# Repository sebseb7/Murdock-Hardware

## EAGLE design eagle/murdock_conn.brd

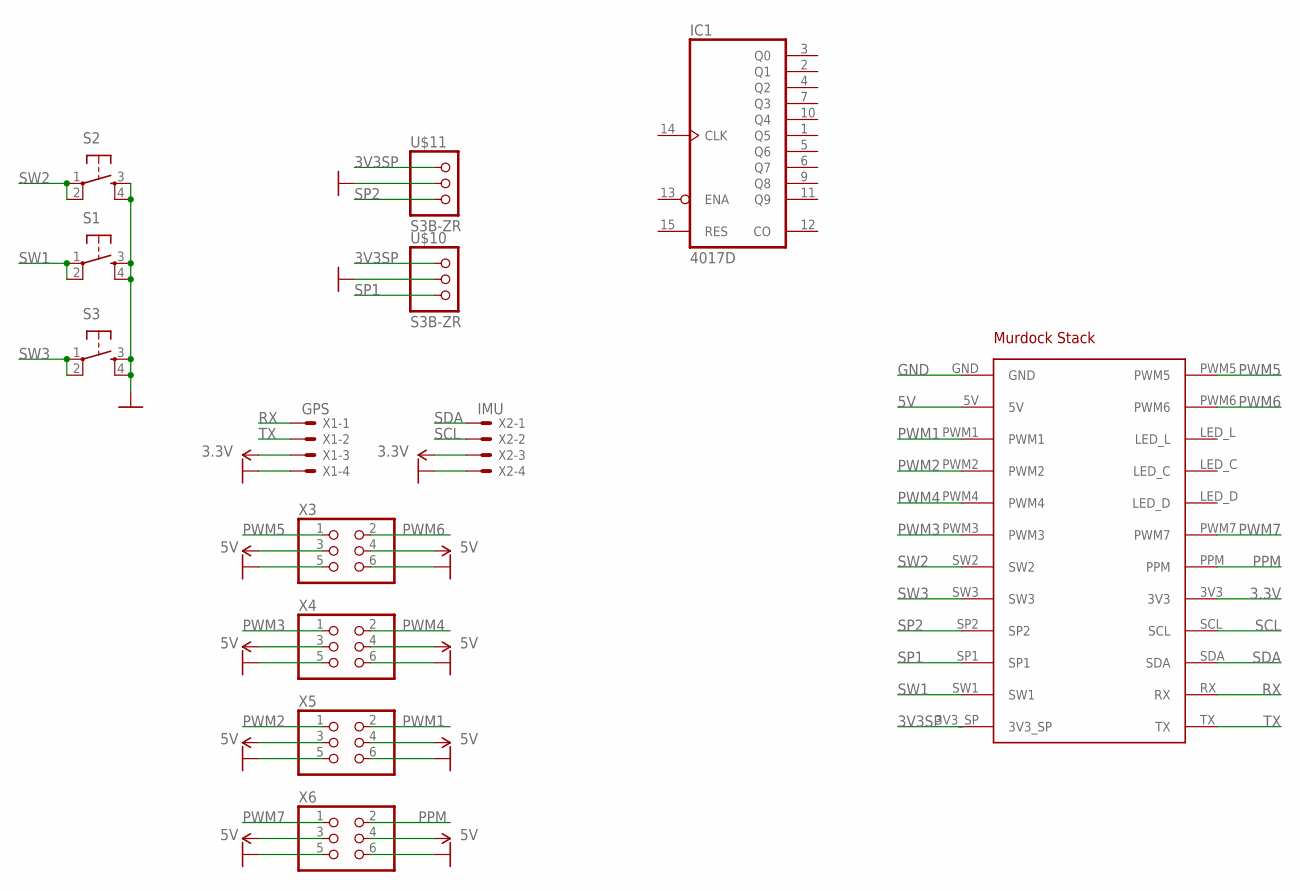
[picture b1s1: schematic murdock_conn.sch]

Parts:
IC1: 4017D; SO16
S1, S2, S3: LSH
U$10, U$11: S3B-ZR
X1: GPS; 70553-04
X2: IMU; 70553-04
X3, X4, X5, X6: PINHD-2X3/90; 2X03/90
X7: MURDOCK_STACK

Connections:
3.3V: X1.3, X2.3, X7.3V3
3V3SP: U$10.1, U$11.1, X7.3V3_SP
5V: X3.3, X3.4, X4.3, X4.4, X5.3, X5.4, X6.3, X6.4, X7.5V
GND: S1.3, S1.4, S2.3, S2.4, S3.3, S3.4, U$10.2, U$11.2, X1.4, X2.4, X3.5, X3.6, X4.5, X4.6, X5.5, X5.6, X6.5, X6.6, X7.GND
PPM: X6.2, X7.PPM
PWM1: X5.2, X7.PWM1
PWM2: X5.1, X7.PWM2
PWM3: X4.1, X7.PWM3
PWM4: X4.2, X7.PWM4
PWM5: X3.1, X7.PWM5
PWM6: X3.2, X7.PWM6
PWM7: X6.1, X7.PWM7
RX: X1.1, X7.RX
SCL: X2.2, X7.SCL
SDA: X2.1, X7.SDA
SP1: U$10.3, X7.SP1
SP2: U$11.3, X7.SP2
SW1: S1.1, S1.2, X7.SW1
SW2: S2.1, S2.2, X7.SW2
SW3: S3.1, S3.2, X7.SW3
TX: X1.2, X7.TX
VDD: IC1.16 (VDD)
VSS: IC1.8 (VSS)

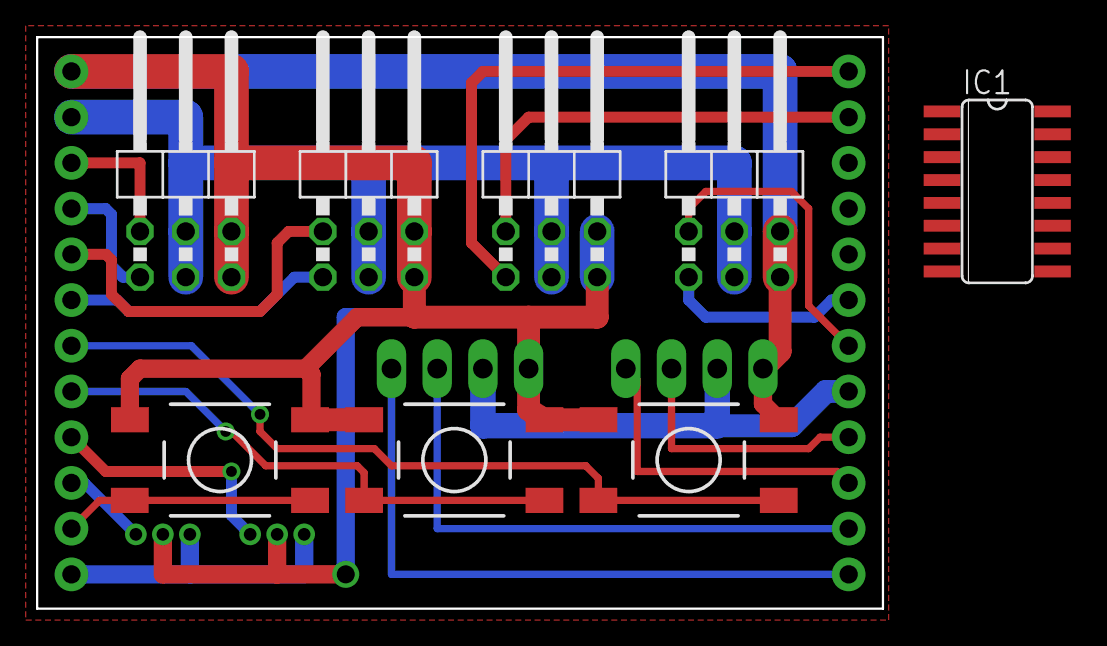
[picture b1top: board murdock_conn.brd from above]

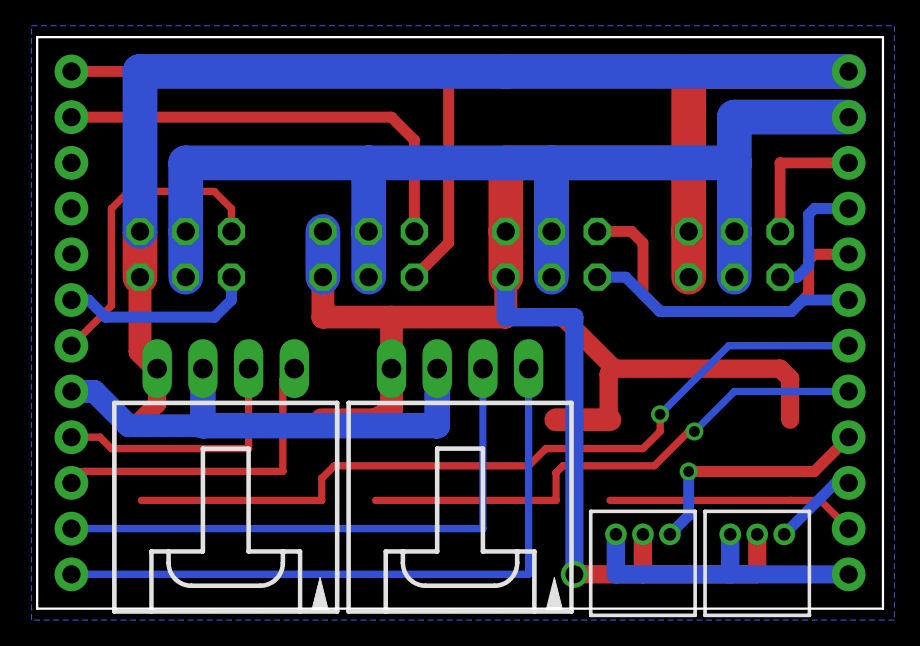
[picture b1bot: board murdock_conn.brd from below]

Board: 2 copper layers, 47.0 x 31.8 mm, 13 parts (4 on the bottom side), 21 nets.

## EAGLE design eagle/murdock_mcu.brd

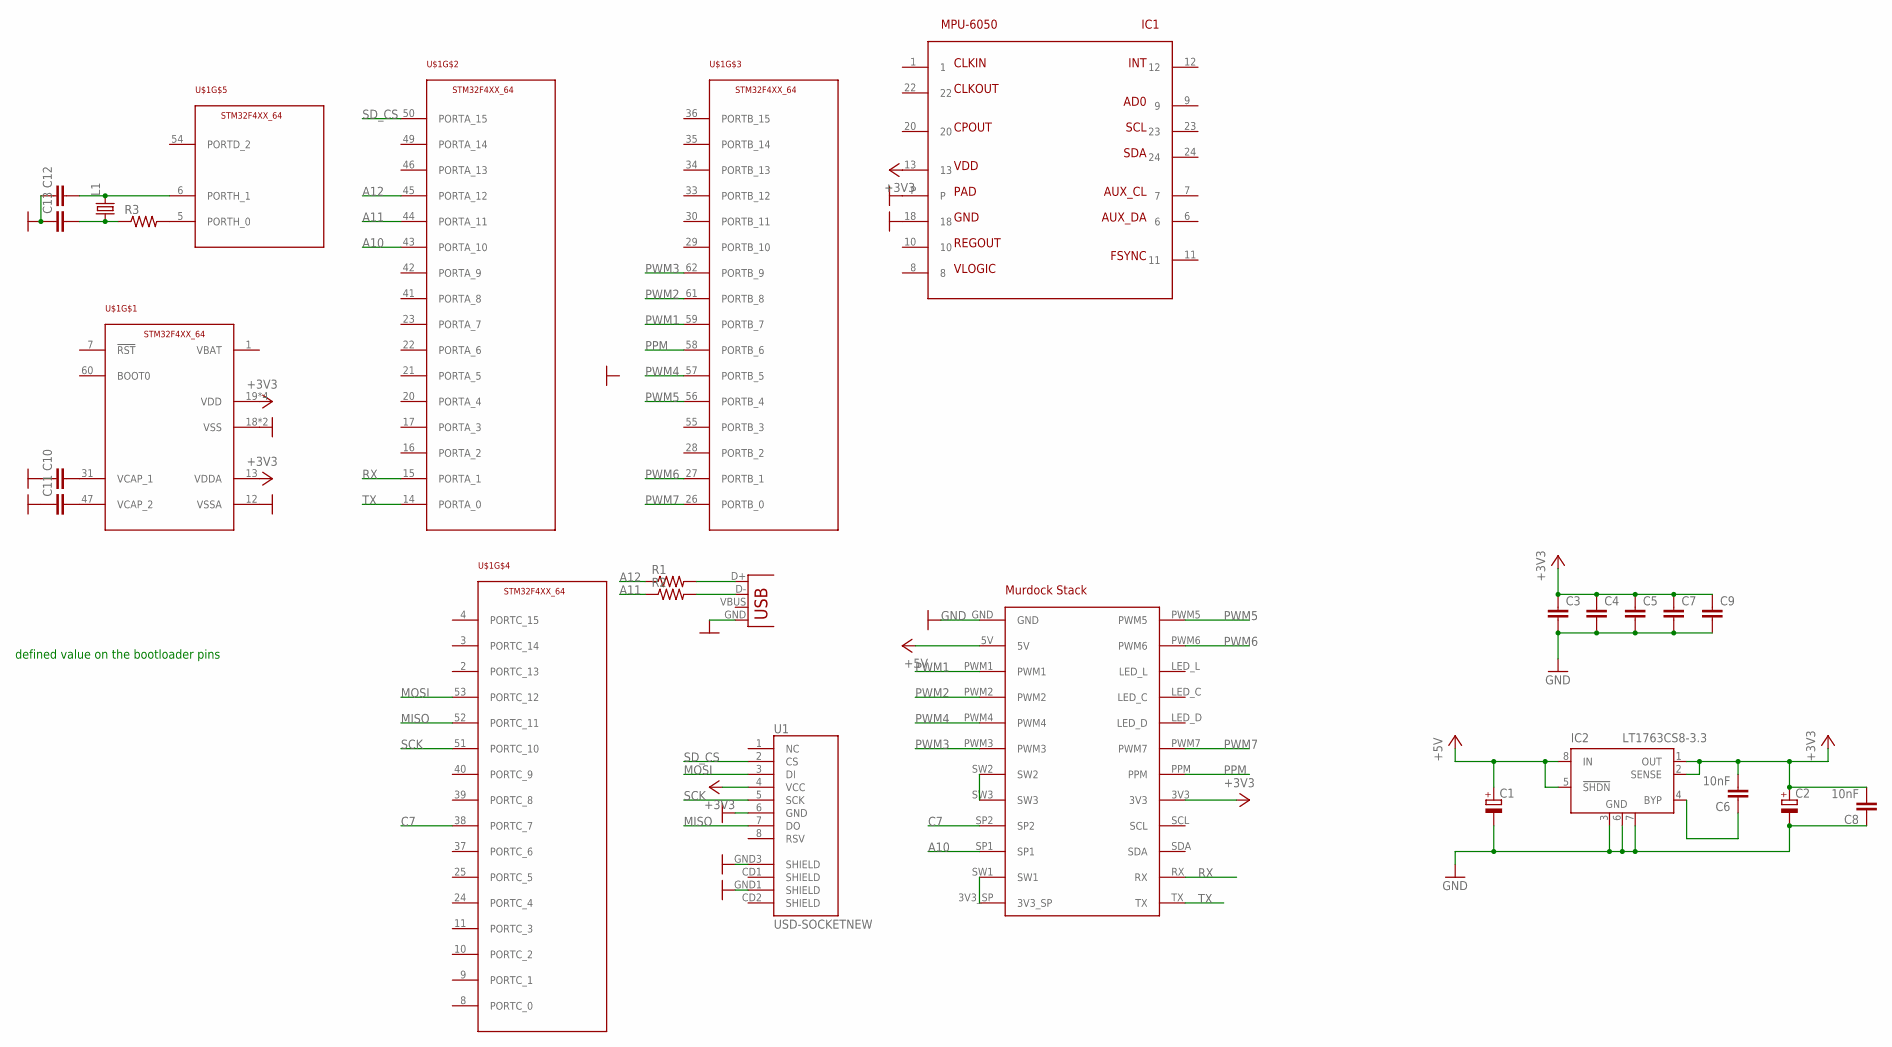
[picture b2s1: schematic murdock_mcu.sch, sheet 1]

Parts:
C1, C2: CPOL-EUSMCD; SMC_D
C3, C4, C5, C7, C9, C12, C13: CAP0402-CAP; 0402-CAP
C6, C8: 10nF; C0402
C10, C11: CAP0805; 0805
IC1: MPU-6050; QFN24
IC2: LT1763CS8-3.3; SOIC8
L1: X22-OSCILLATOR; X22
R1, R2, R3: RESISTOR0402-RES; 0402-RES
U1: USD-SOCKETNEW; MICRO-SD-SOCKET-PP
U$1: STM32F4XX_64; TQFP64
X1: USBSMD; USB-MINIB
X2: MURDOCK_STACK

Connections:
+3V3: C2.+, C3.1, C4.1, C5.1, C6.2, C7.1, C8.2, C9.1, IC1.13, IC2.1 (OUT), IC2.2 (SENSE), U1.4 (VCC), U$1.13 (VDDA), U$1.19 (VDD), U$1.32 (VDD), U$1.48 (VDD), U$1.64 (VDD), X2.3V3
+5V: C1.+, IC2.5 (!SHDN), IC2.8 (IN), X2.5V
A10: U$1.43 (PORTA_10), X2.SP1
A11: R2.1, U$1.44 (PORTA_11)
A12: R1.1, U$1.45 (PORTA_12)
C7: U$1.38 (PORTC_7), X2.SP2
GND: C1.-, C2.-, C3.2, C4.2, C5.2, C7.2, C8.1, C9.2, C10.1, C11.1, C12.1, C13.1, IC1.18, IC1.P, IC2.3 (GND), IC2.6 (GND), IC2.7 (GND), U1.6 (GND), U1.GND1 (SHIELD), U1.GND3 (SHIELD), U$1.12 (VSSA), U$1.18 (VSS), U$1.63 (VSS), X1.GND, X2.GND
MISO: U1.7 (DO), U$1.52 (PORTC_11)
MOSI: U1.3 (DI), U$1.53 (PORTC_12)
unnamed: R2.2, X1.D-
unnamed: R1.2, X1.D+
unnamed: C10.2, U$1.31 (VCAP_1)
unnamed: C11.2, U$1.47 (VCAP_2)
unnamed: R3.2, U$1.5 (PORTH_0)
unnamed: C13.2, L1.1, R3.1
unnamed: C12.2, L1.3 (2), U$1.6 (PORTH_1)
unnamed: X2.3V3_SP, X2.SW1
unnamed: X2.SW2, X2.SW3
unnamed: C6.1, IC2.4 (BYP)
PPM: U$1.58 (PORTB_6), X2.PPM
PWM1: U$1.59 (PORTB_7), X2.PWM1
PWM2: U$1.61 (PORTB_8), X2.PWM2
PWM3: U$1.62 (PORTB_9), X2.PWM3
PWM4: U$1.57 (PORTB_5), X2.PWM4
PWM5: U$1.56 (PORTB_4), X2.PWM5
PWM6: U$1.27 (PORTB_1), X2.PWM6
PWM7: U$1.26 (PORTB_0), X2.PWM7
RX: U$1.15 (PORTA_1), X2.RX
SCK: U1.5 (SCK), U$1.51 (PORTC_10)
SD_CS: U1.2 (CS), U$1.50 (PORTA_15)
TX: U$1.14 (PORTA_0), X2.TX

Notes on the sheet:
defined value on the bootloader pins

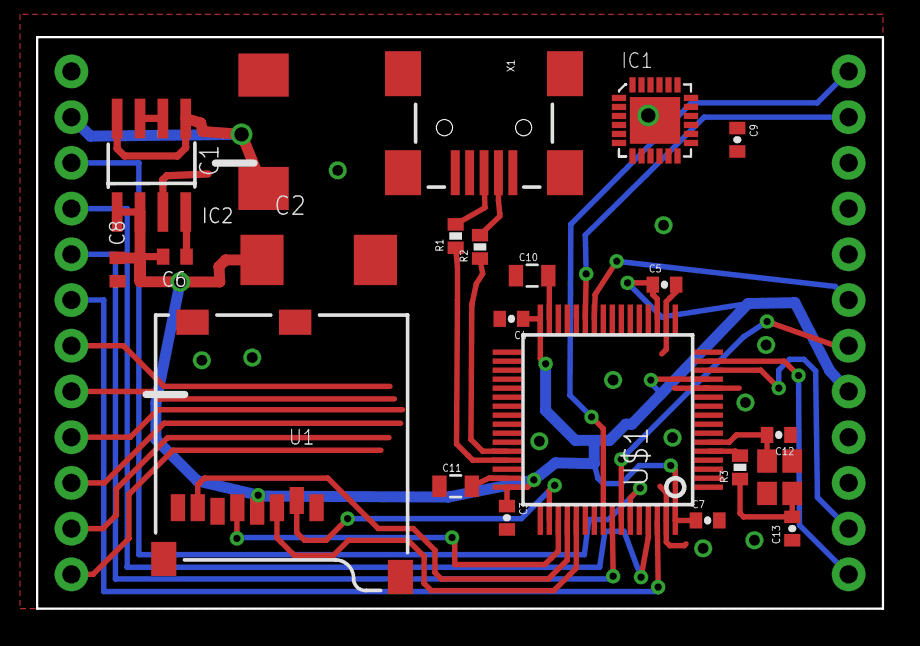
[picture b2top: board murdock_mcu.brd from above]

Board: 2 copper layers, 47.0 x 31.8 mm, 23 parts (0 on the bottom side), 31 nets.

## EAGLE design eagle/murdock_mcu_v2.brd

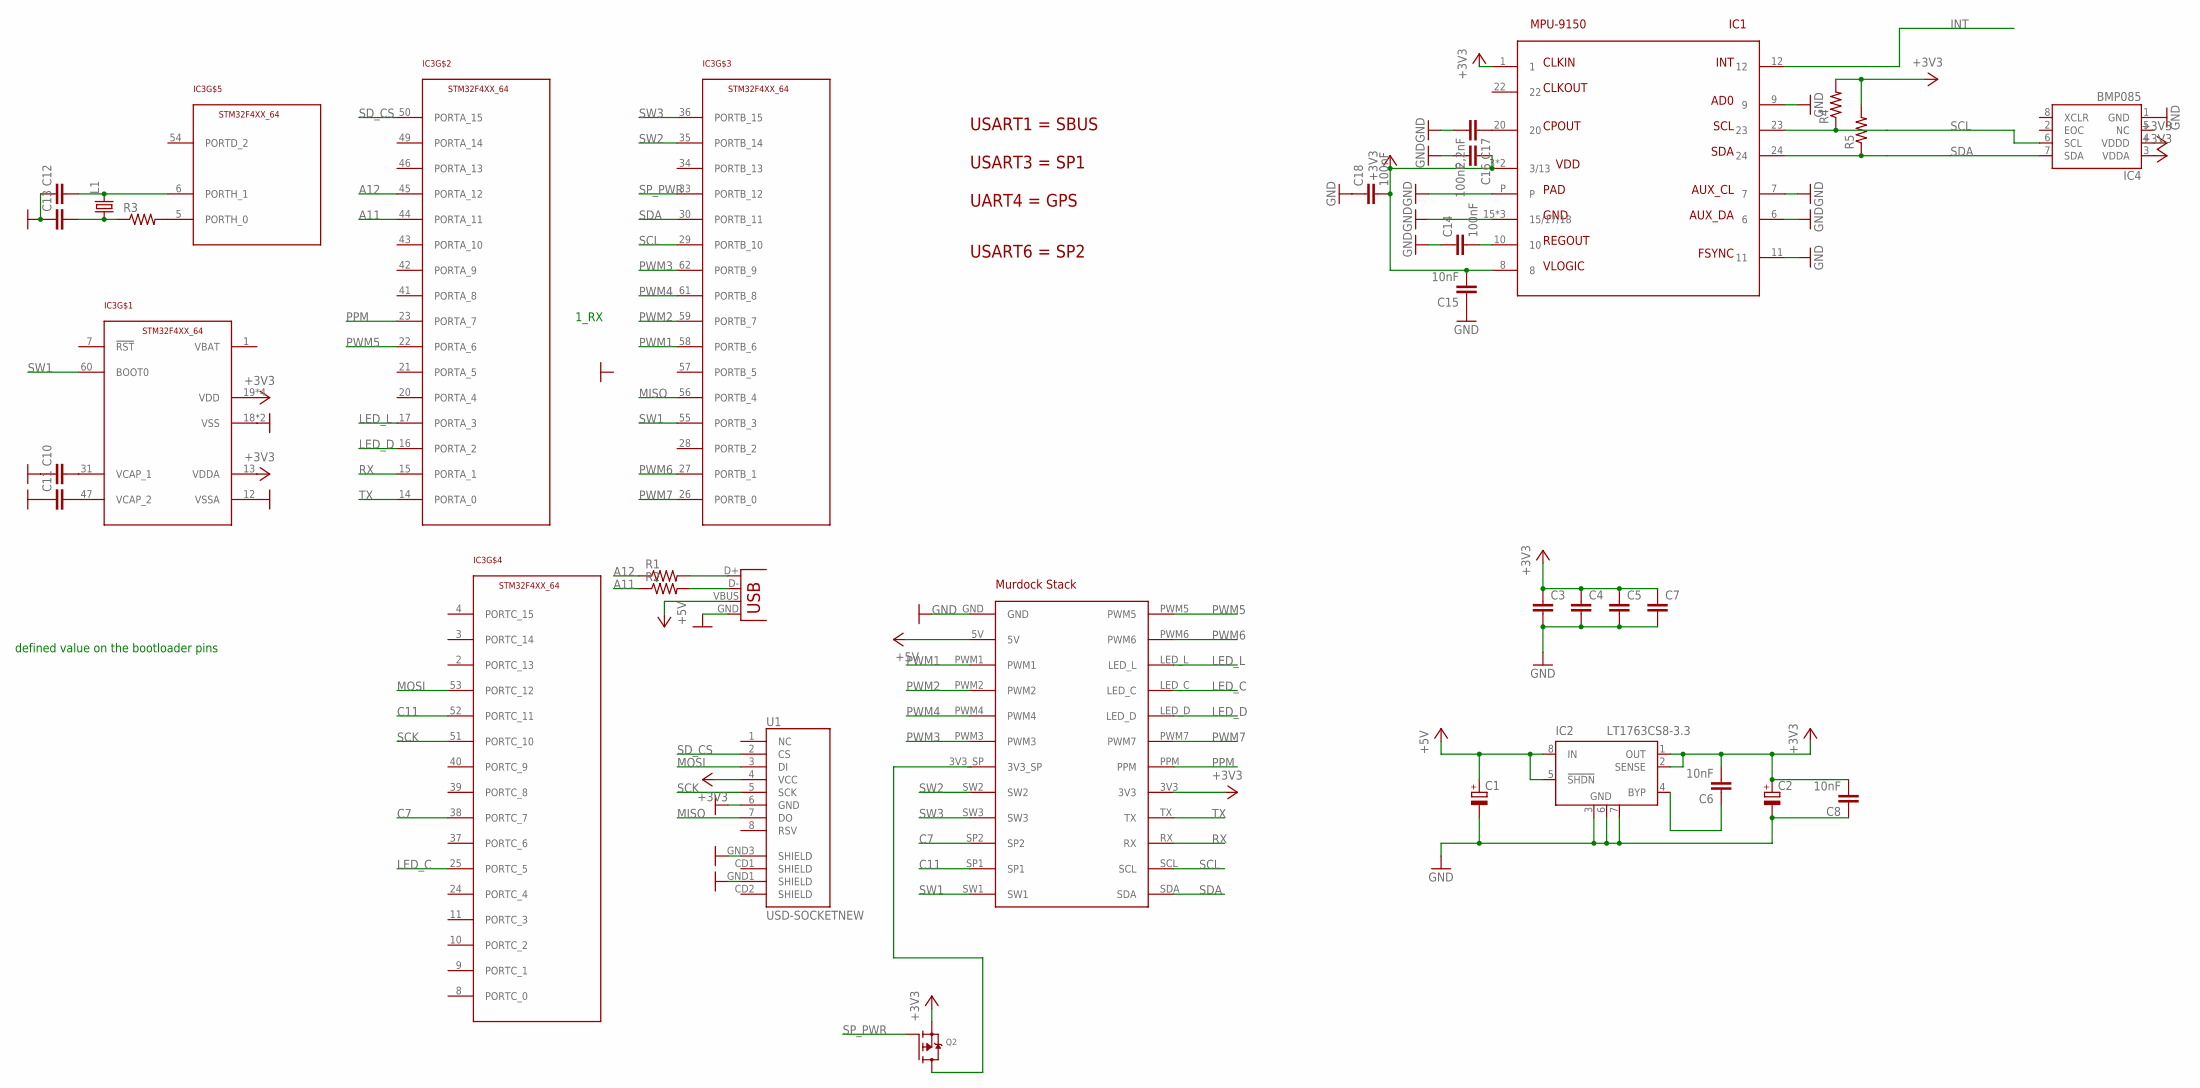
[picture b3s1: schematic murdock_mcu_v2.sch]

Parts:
C1, C2: CPOL-EUSMCD; SMC_D
C3, C4, C5, C7, C12, C13: CAP0402-CAP; 0402-CAP
C6, C8: 10nF; C0402
C10, C11: CAP0805; 0805
C14, C16, C18: 100nF; 0402-CAP
C15: 10nF; 0402-CAP
C17: 2,2nF; 0402-CAP
IC1: MPU-9150; QFN24
IC2: LT1763CS8-3.3; SOIC8
IC3: STM32F4XX_64; TQFP64
IC4: BMP085
L1: X22-OSCILLATOR; X22
Q2: MOSFET-P; SOT23-R
R1, R2, R3, R4, R5: RESISTOR0402-RES; 0402-RES
U1: USD-SOCKETNEW; MICRO-SD-SOCKET-PP
X1: USBSMD; USB-MINIB
X2: MURDOCK_STACK

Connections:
+3V3: C2.+, C3.1, C4.1, C5.1, C6.2, C7.1, C8.2, C15.2, C16.1, C18.2, IC1.1, IC1.3 (3/13), IC1.8, IC1.13 (3/13), IC2.1 (OUT), IC2.2 (SENSE), IC3.13 (VDDA), IC3.19 (VDD), IC3.32 (VDD), IC3.48 (VDD), IC3.64 (VDD), IC4.3 (VDDA), IC4.4 (VDDD), Q2.2 (S), R4.2, R5.2, U1.4 (VCC), X2.3V3
+5V: C1.+, IC2.5 (!SHDN), IC2.8 (IN), X1.VBUS, X2.5V
A11: IC3.44 (PORTA_11), R2.1
A12: IC3.45 (PORTA_12), R1.1
C7: IC3.38 (PORTC_7), X2.SP2
C11: IC3.52 (PORTC_11), X2.SP1
GND: C1.-, C2.-, C3.2, C4.2, C5.2, C7.2, C8.1, C10.1, C11.1, C12.1, C13.1, C14.1, C15.1, C16.2, C17.2, C18.1, IC1.6, IC1.7, IC1.9, IC1.11, IC1.15 (15/17/18), IC1.17 (15/17/18), IC1.18 (15/17/18), IC1.P, IC2.3 (GND), IC2.6 (GND), IC2.7 (GND), IC3.12 (VSSA), IC3.18 (VSS), IC3.63 (VSS), IC4.1 (GND), U1.6 (GND), U1.GND1 (SHIELD), U1.GND3 (SHIELD), X1.GND, X2.GND
INT: IC1.12
LED_C: IC3.25 (PORTC_5), X2.LED_C
LED_D: IC3.16 (PORTA_2), X2.LED_D
LED_L: IC3.17 (PORTA_3), X2.LED_L
MISO: IC3.56 (PORTB_4), U1.7 (DO)
MOSI: IC3.53 (PORTC_12), U1.3 (DI)
unnamed: R2.2, X1.D-
unnamed: R1.2, X1.D+
unnamed: C10.2, IC3.31 (VCAP_1)
unnamed: C11.2, IC3.47 (VCAP_2)
unnamed: IC3.5 (PORTH_0), R3.2
unnamed: C13.2, L1.1, R3.1
unnamed: C12.2, IC3.6 (PORTH_1), L1.3 (2)
unnamed: Q2.3 (D), X2.3V3_SP
unnamed: C14.2, IC1.10
unnamed: C17.1, IC1.20
unnamed: C6.1, IC2.4 (BYP)
PPM: IC3.23 (PORTA_7), X2.PPM
PWM1: IC3.58 (PORTB_6), X2.PWM1
PWM2: IC3.59 (PORTB_7), X2.PWM2
PWM3: IC3.62 (PORTB_9), X2.PWM3
PWM4: IC3.61 (PORTB_8), X2.PWM4
PWM5: IC3.22 (PORTA_6), X2.PWM5
PWM6: IC3.27 (PORTB_1), X2.PWM6
PWM7: IC3.26 (PORTB_0), X2.PWM7
RX: IC3.15 (PORTA_1), X2.RX
SCK: IC3.51 (PORTC_10), U1.5 (SCK)
SCL: IC1.23, IC3.29 (PORTB_10), IC4.6 (SCL), R4.1, X2.SCL
SDA: IC1.24, IC3.30 (PORTB_11), IC4.7 (SDA), R5.1, X2.SDA
SD_CS: IC3.50 (PORTA_15), U1.2 (CS)
SP_PWR: IC3.33 (PORTB_12), Q2.1 (G)
SW1: IC3.55 (PORTB_3), IC3.60 (BOOT0), X2.SW1
SW2: IC3.35 (PORTB_14), X2.SW2
SW3: IC3.36 (PORTB_15), X2.SW3
TX: IC3.14 (PORTA_0), X2.TX

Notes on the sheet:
defined value on the bootloader pins
UART4 = GPS
USART1 = SBUS
USART6 = SP2
USART3 = SP1
1_RX

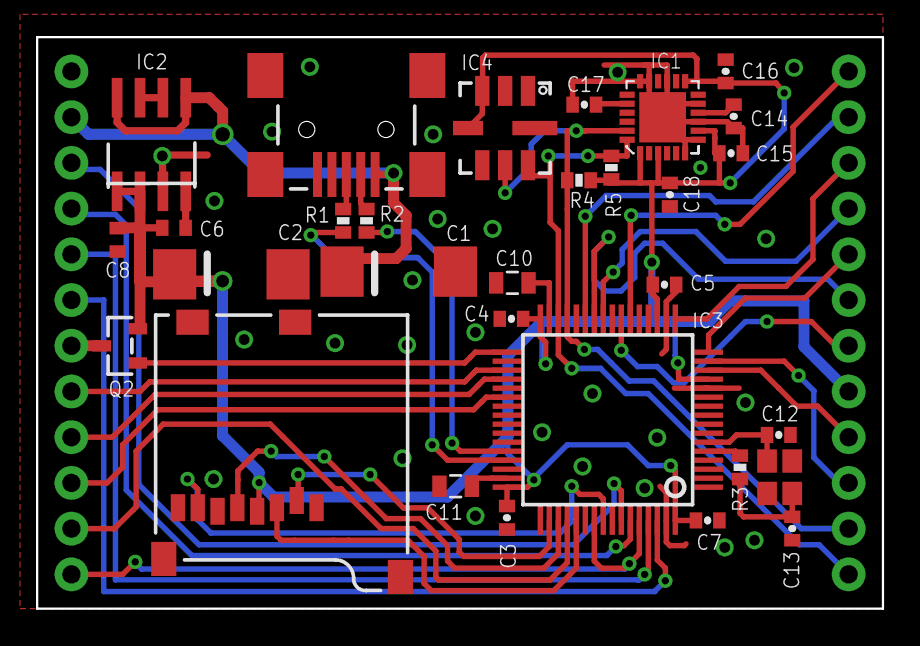
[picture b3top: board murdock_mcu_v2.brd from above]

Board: 2 copper layers, 47.0 x 31.8 mm, 32 parts (1 on the bottom side), 41 nets.

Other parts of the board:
U$1: C3D2_LOGO_SMALL

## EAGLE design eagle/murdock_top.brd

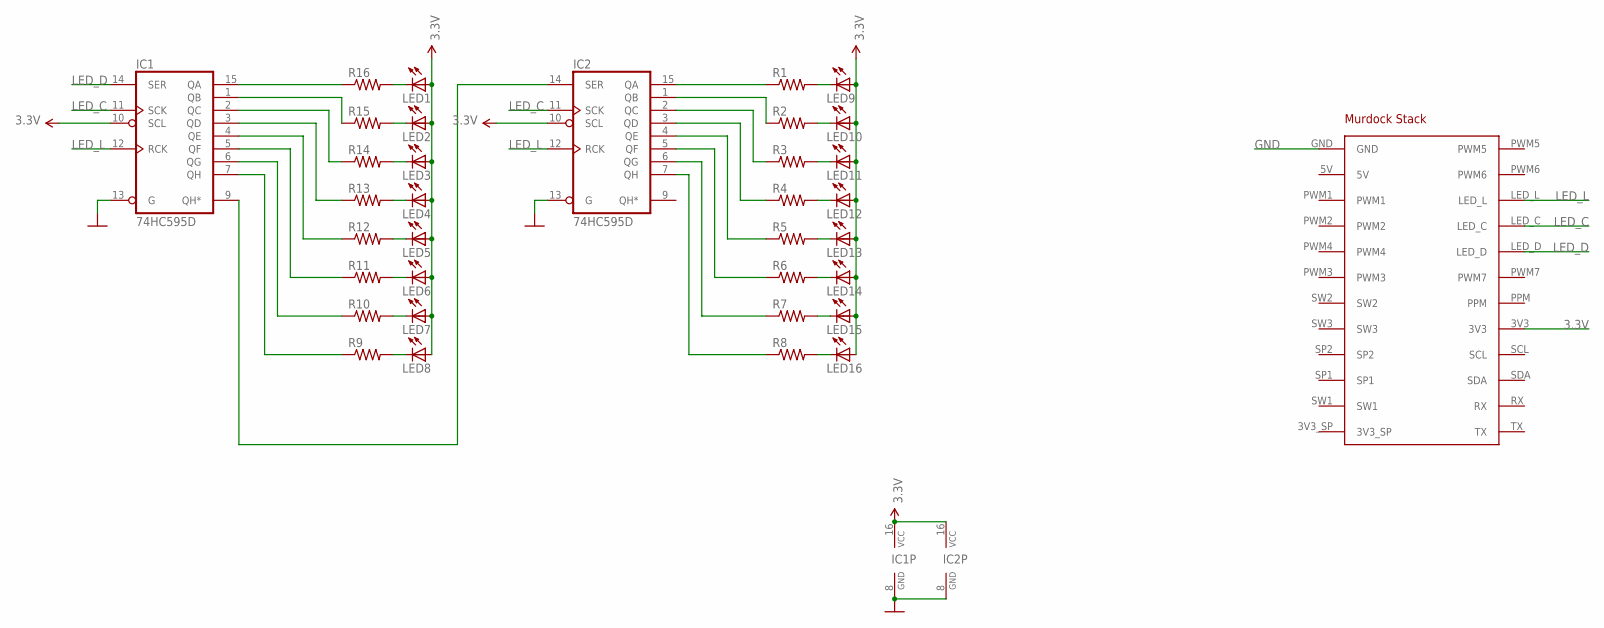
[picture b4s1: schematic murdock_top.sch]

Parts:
IC1, IC2: 74HC595D; SO16
LED1, LED2, LED3, LED4, LED5, LED6, LED7, LED8, LED9, LED10, LED11, LED12, LED13, LED14, LED15, LED16: LGM47K
R1, R2, R3, R4, R5, R6, R7, R8, R9, R10, R11, R12, R13, R14, R15, R16: RESISTOR0402-RES; 0402-RES
X1: MURDOCK_STACK

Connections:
3.3V: IC1.10 (SCL), IC1.16 (VCC), IC2.10 (SCL), IC2.16 (VCC), LED1.A, LED2.A, LED3.A, LED4.A, LED5.A, LED6.A, LED7.A, LED8.A, LED9.A, LED10.A, LED11.A, LED12.A, LED13.A, LED14.A, LED15.A, LED16.A, X1.3V3
GND: IC1.8 (GND), IC1.13 (G), IC2.8 (GND), IC2.13 (G), X1.GND
LED_C: IC1.11 (SCK), IC2.11 (SCK), X1.LED_C
LED_D: IC1.14 (SER), X1.LED_D
LED_L: IC1.12 (RCK), IC2.12 (RCK), X1.LED_L
unnamed: IC1.9 (QH*), IC2.14 (SER)
unnamed: LED9.K (C), R1.2
unnamed: LED10.K (C), R2.2
unnamed: LED11.K (C), R3.2
unnamed: LED12.K (C), R4.2
unnamed: LED13.K (C), R5.2
unnamed: LED14.K (C), R6.2
unnamed: LED15.K (C), R7.2
unnamed: LED16.K (C), R8.2
unnamed: LED1.K (C), R16.2
unnamed: LED2.K (C), R15.2
unnamed: LED3.K (C), R14.2
unnamed: LED4.K (C), R13.2
unnamed: LED5.K (C), R12.2
unnamed: LED6.K (C), R11.2
unnamed: LED7.K (C), R10.2
unnamed: LED8.K (C), R9.2
Q0: IC2.15 (QA), R1.1
Q1: IC2.1 (QB), R2.1
Q2: IC2.2 (QC), R3.1
Q3: IC2.3 (QD), R4.1
Q4: IC2.4 (QE), R5.1
Q5: IC2.5 (QF), R6.1
Q6: IC2.6 (QG), R7.1
Q7: IC2.7 (QH), R8.1
QA: IC1.15 (QA), R16.1
QB: IC1.1 (QB), R15.1
QC: IC1.2 (QC), R14.1
QD: IC1.3 (QD), R13.1
QE: IC1.4 (QE), R12.1
QF: IC1.5 (QF), R11.1
QG: IC1.6 (QG), R10.1
QH: IC1.7 (QH), R9.1

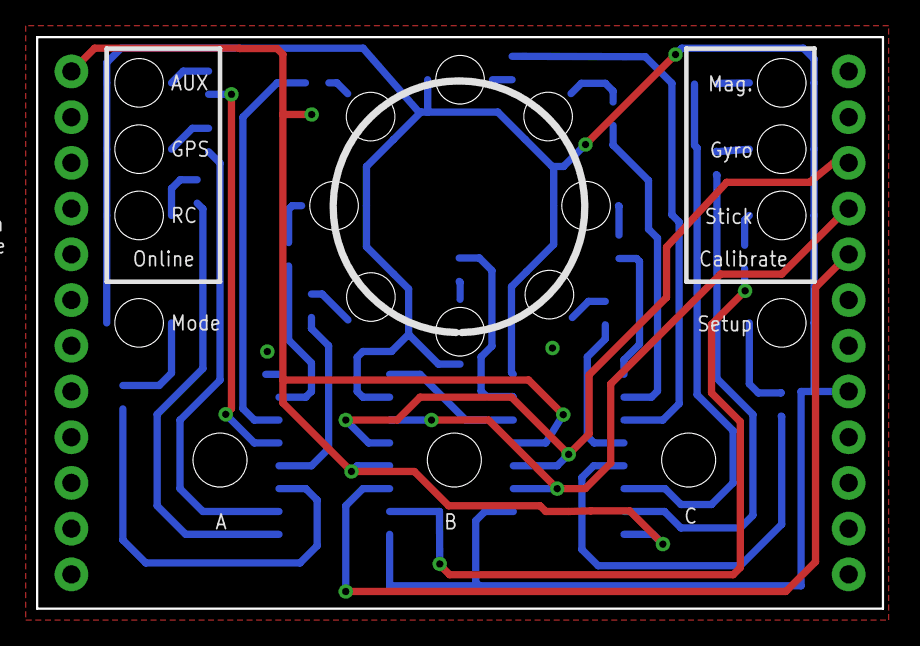
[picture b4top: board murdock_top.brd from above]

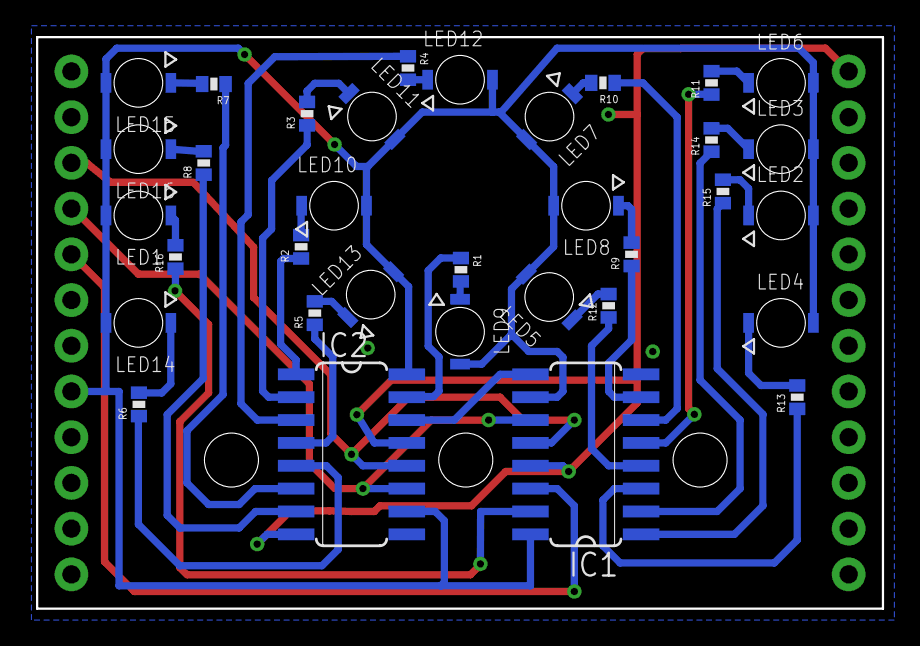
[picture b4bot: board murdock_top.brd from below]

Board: 2 copper layers, 47.0 x 31.8 mm, 35 parts (34 on the bottom side), 38 nets.

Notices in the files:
parts and their libraries:
SparkFun-Aesthetics: Licensing: CC v3.0 Share-Alike You are welcome to use this library for commercial purposes.
microbuilder: This work is placed in the public domain, and may be freely used for commercial and non-commercial work with the following conditions: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
